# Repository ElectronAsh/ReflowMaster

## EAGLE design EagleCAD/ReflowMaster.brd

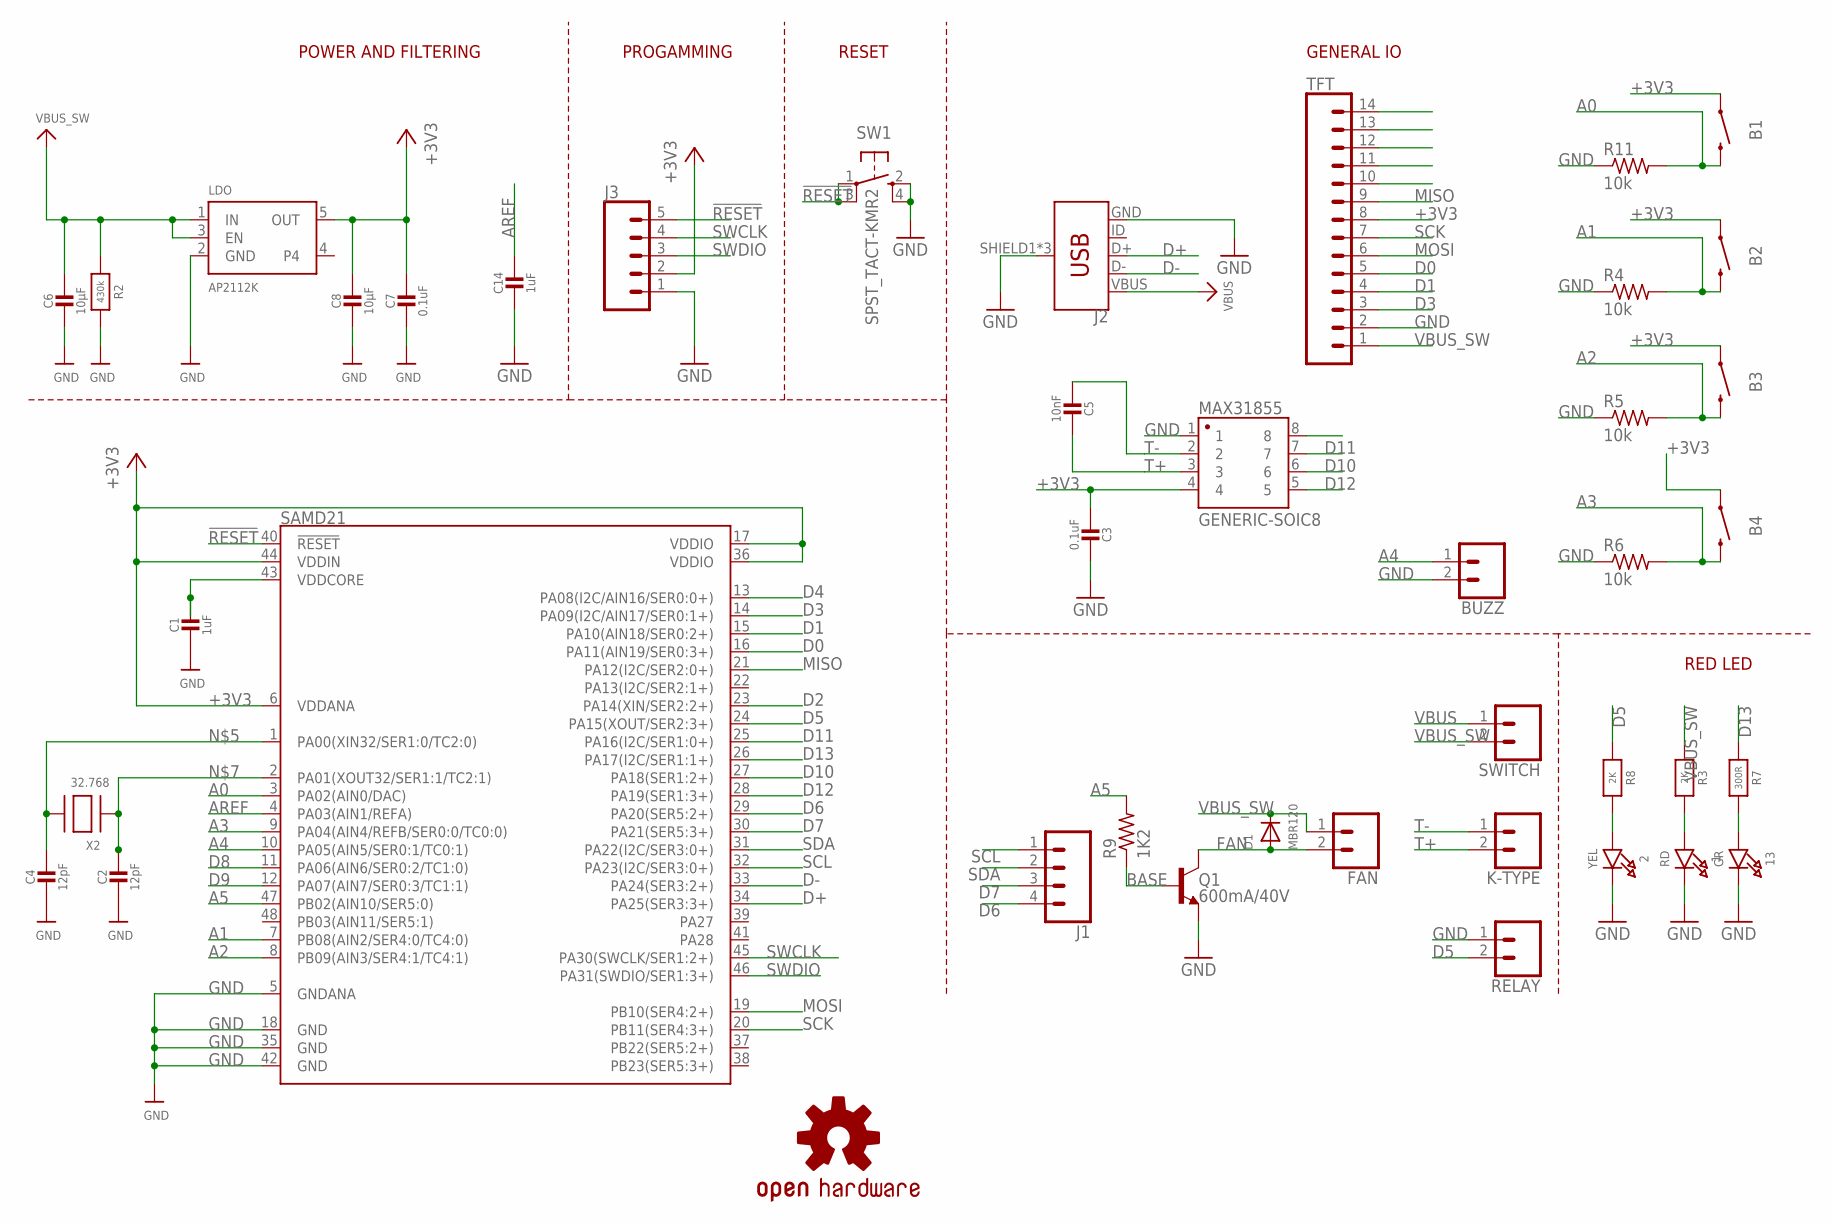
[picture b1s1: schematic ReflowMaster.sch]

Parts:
1: RD; CHIPLED_0805_NOOUTLINE
2: YEL; CHIPLED_0805_NOOUTLINE
13: GR; CHIPLED_0805_NOOUTLINE
B1, B2, B3, B4: MOMENTARY-SWITCH-SPST-PTH-RIGHT-ANGLE-KIT; TACTILE_SWITCH_PTH_RIGHT_ANGLE_KIT
BUZZ: CONN_02; 1X02
C1, C14: 1uF; 0805-NO
C2, C4: 12pF; 0805-NO
C3, C7: 0.1uF; 0805-NO
C5: 10nF; 0805-NO
C6, C8: 10µF; 0805-NO
D1: MBR120; SOD-123
FAN: CONN_02; 1X02
J1: CONN_041X04_NO_SILK; 1X04_NO_SILK
J2: USB_MICRO-B_FEMALE-SMT; USB-B-MICRO-SMD
J3: CONN_05NO_SILK; 1X05_NO_SILK
K-TYPE: CONN_02; 1X02
LDO: AP2112K; SOT23-5
LOGO1: OSHW-LOGOS; OSHW-LOGO-S
MAX31855: GENERIC-SOIC8; SO08-UNIVERSAL
Q1: 600mA/40V; SOT23-3
R2: 430k; 0805-NO
R3, R8: 2K; 0805-NO
R4, R5, R6, R11: 10k; R0805
R7: 300R; 0805-NO
R9: 1K2; R0805
RELAY: CONN_02; 1X02
SAMD21: ATSAMD21G-A; TQFP-48
SW1: SPST_TACT-KMR2; KMR2
SWITCH: CONN_02; 1X02
TFT: CONN_14NO_SILK; 1X14_NO_SILK
X2: 32.768; XTAL3215

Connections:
!RESET: J3.5, SAMD21.40 (!RESET!), SW1.1, SW1.3 (P1)
+3V3: B1.1, B2.1, B3.1, B4.1, C3.2, C7.1, C8.1, J3.2, LDO.5 (OUT), MAX31855.4, SAMD21.6 (VDDANA), SAMD21.17 (VDDIO), SAMD21.36 (VDDIO), SAMD21.44 (VDDIN), TFT.8
A0: B1.2, R11.2, SAMD21.3 (PA02(AIN0/DAC))
A1: B2.2, R4.2, SAMD21.7 (PB08(AIN2/SER4:0/TC4:0))
A2: B3.2, R5.2, SAMD21.8 (PB09(AIN3/SER4:1/TC4:1))
A3: B4.2, R6.2, SAMD21.9 (PA04(AIN4/REFB/SER0:0/TC0:0))
A4: BUZZ.1, SAMD21.10 (PA05(AIN5/SER0:1/TC0:1))
A5: R9.2, SAMD21.47 (PB02(AIN10/SER5:0))
AREF: C14.1, SAMD21.4 (PA03(AIN1/REFA))
BASE: Q1.1 (B), R9.1
D0: SAMD21.16 (PA11(AIN19/SER0:3+)), TFT.5
D1: SAMD21.15 (PA10(AIN18/SER0:2+)), TFT.4
D2: SAMD21.23 (PA14(XIN/SER2:2+))
D3: SAMD21.14 (PA09(I2C/AIN17/SER0:1+)), TFT.3
D4: SAMD21.13 (PA08(I2C/AIN16/SER0:0+))
D5: R8.1, RELAY.2, SAMD21.24 (PA15(XOUT/SER2:3+))
D6: J1.4, SAMD21.29 (PA20(SER5:2+))
D7: J1.3, SAMD21.30 (PA21(SER5:3+))
D8: SAMD21.11 (PA06(AIN6/SER0:2/TC1:0))
D9: SAMD21.12 (PA07(AIN7/SER0:3/TC1:1))
D10: MAX31855.6, SAMD21.27 (PA18(SER1:2+))
D11: MAX31855.7, SAMD21.25 (PA16(I2C/SER1:0+))
D12: MAX31855.5, SAMD21.28 (PA19(SER1:3+))
D13: R7.1, SAMD21.26 (PA17(I2C/SER1:1+))
D+: J2.D+, SAMD21.34 (PA25(SER3:3+))
D-: J2.D-, SAMD21.33 (PA24(SER3:2+))
FAN: D1.A, FAN.2, Q1.3 (C)
GND: 1.C, 2.C, 13.C, BUZZ.2, C1.2, C2.2, C3.1, C4.2, C6.2, C7.2, C8.2, C14.2, J2.GND, J2.SHIELD1 (SHIELD), J2.SHIELD2 (SHIELD), J2.SHIELD3 (SHIELD), J3.1, LDO.2 (GND), MAX31855.1, Q1.2 (E), R2.2, R4.1, R5.1, R6.1, R11.1, RELAY.1, SAMD21.5 (GNDANA), SAMD21.18 (GND), SAMD21.35 (GND), SAMD21.42 (GND), SW1.2 (S), SW1.4 (S1), TFT.2
MISO: SAMD21.21 (PA12(I2C/SER2:0+)), TFT.9
MOSI: SAMD21.19 (PB10(SER4:2+)), TFT.6
unnamed: 1.A, R3.2
unnamed: 13.A, R7.2
unnamed: 2.A, R8.2
unnamed: C4.1, SAMD21.1 (PA00(XIN32/SER1:0/TC2:0)), X2.P$2
unnamed: C2.1, SAMD21.2 (PA01(XOUT32/SER1:1/TC2:1)), X2.P$1
SCK: SAMD21.20 (PB11(SER4:3+)), TFT.7
SCL: J1.1, SAMD21.32 (PA23(I2C/SER3:0+))
SDA: J1.2, SAMD21.31 (PA22(I2C/SER3:0+))
SWCLK: J3.4, SAMD21.45 (PA30(SWCLK/SER1:2+))
SWDIO: J3.3, SAMD21.46 (PA31(SWDIO/SER1:3+))
T+: C5.1, K-TYPE.2, MAX31855.3
T-: C5.2, K-TYPE.1, MAX31855.2
VBUS: J2.VBUS, SWITCH.1
VBUS_SW: C6.1, D1.C, FAN.1, LDO.1 (IN), LDO.3 (EN), R2.1, R3.1, SWITCH.2, TFT.1
VDDCORE: C1.1, SAMD21.43 (VDDCORE)

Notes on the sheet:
POWER AND FILTERING
RESET
GENERAL IO
RED LED
PROGAMMING

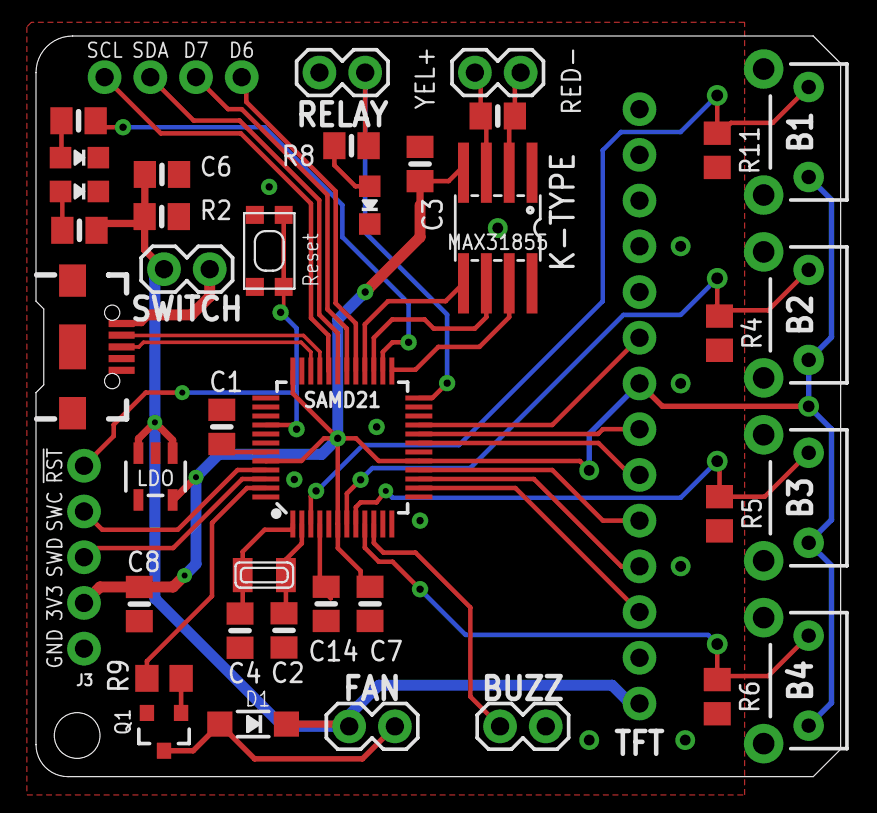
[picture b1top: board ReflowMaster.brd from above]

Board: 2 copper layers, 44.7 x 41.1 mm, 42 parts (1 on the bottom side), 41 nets.

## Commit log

2019-08-04 added a programming header + PCB tweaks

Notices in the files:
EagleCAD/ReflowMaster.sch:
COPYRIGHT: 2018
parts and their libraries:
microbuilder: This work is placed in the public domain, and may be freely used for commercial and non-commercial work with the following conditions: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
SparkFun-IC-Microcontroller: Licensing: Creative Commons ShareAlike 4.0 International - https://creativecommons.org/licenses/by-sa/4.0
